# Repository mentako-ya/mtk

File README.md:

# mtk

homebrew keyboard with thumb operated trackball & rotary encoder.

mtk64el 作例
- キーキャップ:CORSAIR PBT DOUBLE-SHOT 交換用カラーキーキャップセット - 日本語108キー, Arctic White - CH-9911040-JP
- トラックボール：ぺリックス PERIPRO-303 GP 34 mm
- TRRSケーブル：https://shop.dailycraft.jp/products/trrs_cable_50_gloss
- USB Type-cケーブル：https://amzn.asia/d/h8pfZIJ

mtk64el ロープロファイル 作例

mtk64el ロープロファイル(Lofree + Chock V1) 作例
- キースイッチ(メイン部分):[LOFREE x KAILH Full POM Low Profile Switches](https://amzn.asia/d/74pwfkn)
- キーキャップ(メイン部分):[XVX ロープロファイル PBT キーキャップ](https://amzn.asia/d/7V1A6T4)
- キースイッチ(親指部分):[Kailhロープロファイルスイッチ - Pink](https://amzn.asia/d/bSlNIMm)
- キーキャップ(親指部分):[Chocfox CFX keycap](https://talpkeyboard.net/items/638b518dcc223746ee14eae8)

mtk64el Lofree Full POM ロープロファイルスイッチ取り付け例
- [LOFREE x KAILH Full POM Low Profile Switches](https://amzn.asia/d/74pwfkn)

mtk64el MX互換キースイッチ取り付け用トッププレート

mtk64el アンダーグロー

[rev3ケースプリント用3Dデータ](mtk/design/mtk64elt_STL/rev3)　/ テントスタンド[3Dデータ右](mtk/design/mtk64elt_STL/rev3/mtk64el_rev3_tent_RH.stl)　/ [3Dデータ左](mtk/design/mtk64elt_STL/rev3/mtk64el_rev3_tent_LH.stl) 

Chock V1スイッチ / Lofree Shadowスイッチ / MX互換スイッチ

[insnote](https://insnote.net)様にてmtk64eのレビューを掲載いただきました。　https://insnote.net/homebrewkeyboard-mtk64e_review/

mtk64eの使用感、カスタマイズなどご紹介いただいております。導入をご検討されている方はぜひご一読ください。

## remap対応 ファームウェア  

!!! Remap https://remap-keys.app のアップデートにより、従来のファームウェア（qmk_firmware 0.16ベース）を使用したキーボードを接続すると、エラーメッセージが表示されマッピング変更ができません。
https://remap-keys.app をご利用の場合、qmk_firmware 0.22ベースのファームウェアをご使用ください。

### qmk_firmware 0.22ベース ファームウェア https://remap-keys.app をご使用ください

#### PMW3389センサー用
<details>

- [mtk_mtk64e_PMW3389_AutoMouseLayer_via.0.22.hex](https://raw.githubusercontent.com/mentako-ya/mtk/main/mtk/mtk_mtk64e_PMW3389_AutoMouseLayer_via.0.22.hex)
 rev3基板 PMW3389センサー　左ロータリーエンコーダー、右ボール用、自動マウスレイヤー切替

- [mtk_mtk64e_PMW3389_AutoMouseLayer_via_leftball.0.22.hex](https://raw.githubusercontent.com/mentako-ya/mtk/main/mtk/mtk_mtk64e_PMW3389_AutoMouseLayer_via_leftball.0.22.hex)
 rev3基板 PMW3389センサー　右ロータリーエンコーダー、左ボール用、自動マウスレイヤー切替

- [mtk_mtk64e_PMW3389_AutoMouseLayer_via_db.0.22.hex](https://raw.githubusercontent.com/mentako-ya/mtk/main/mtk/mtk_mtk64e_PMW3389_AutoMouseLayer_via_db.0.22.hex)
 rev3基板 PMW3389センサー　左右ボール用、自動マウスレイヤー切替

- [mtk_mtk64e_PMW3389_AutoMouseLayer_via_db.0.22.hex](https://raw.githubusercontent.com/mentako-ya/mtk/main/mtk/mtk_mtk64e_PMW3389_AutoMouseLayer_via_db.0.22.hex)
 rev3基板 PMW3389センサー　左右ボール用（Master側ポインター、Slabe側スクロール）、自動マウスレイヤー切替

- [mtk_mtk64e_PMW3389_AutoMouseLayer_via_db.0.22.hex](https://raw.githubusercontent.com/mentako-ya/mtk/main/mtk/mtk_mtk64e_PMW3389_AutoMouseLayer_via_db_noscrl.0.22.hex)
 rev3基板 PMW3389センサー　左右ボール用（両側ポインター）、自動マウスレイヤー切替

</details>

#### PMW3360センサー用
<details>

- [mtk_mtk64e_PMW3360_AutoMouseLayer_via.0.22.hex](https://raw.githubusercontent.com/mentako-ya/mtk/main/mtk/mtk_mtk64e_PMW3360_AutoMouseLayer_via.0.22.hex)
 rev2基板 PMW3360センサー　左ロータリーエンコーダー、右ボール用、自動マウスレイヤー切替

- [mtk_mtk64e_PMW3360_AutoMouseLayer_via_leftball.0.22.hex](https://raw.githubusercontent.com/mentako-ya/mtk/main/mtk/mtk_mtk64e_PMW3360_AutoMouseLayer_via_leftball.0.22.hex)
 rev2基板 PMW3360センサー　右ロータリーエンコーダー、左ボール用、自動マウスレイヤー切替

- [mtk_mtk64e_PMW3360_AutoMouseLayer_via_db.0.22.hex](https://raw.githubusercontent.com/mentako-ya/mtk/main/mtk/mtk_mtk64e_PMW3360_AutoMouseLayer_via_db.0.22.hex)
 rev2基板 PMW3360センサー　左右ボール用、自動マウスレイヤー切替

- [mtk_mtk64e_PMW3360_AutoMouseLayer_via_db.0.22.hex](https://raw.githubusercontent.com/mentako-ya/mtk/main/mtk/mtk_mtk64e_PMW3360_AutoMouseLayer_via_db.0.22.hex)
 rev2基板 PMW3360センサー　左右ボール用（Master側ポインター、Slabe側スクロール）、自動マウスレイヤー切替

- [mtk_mtk64e_PMW3360_AutoMouseLayer_via_db.0.22.hex](https://raw.githubusercontent.com/mentako-ya/mtk/main/mtk/mtk_mtk64e_PMW3360_AutoMouseLayer_via_db_noscrl.0.22.hex)
 rev2基板 PMW3360センサー　左右ボール用（両側ポインター）、自動マウスレイヤー切替

</details>

!!! qmk_firmware 0.16ベースのファームウェアでRemapをご使用の場合、旧バージョンのRemap https://qmk018.remap-keys.app をご利用ください。

### qmk_firmware 0.16ベース ファームウェア https://qmk018.remap-keys.app を使用
<details>

- [mtk_mtk64_via.hex](https://raw.githubusercontent.com/mentako-ya/mtk/main/mtk/mtk_mtk64_via.hex)
 rev1基板　右ボール/左ボール/左右ボール用
   
- [mtk_mtk64e_via.hex](https://raw.githubusercontent.com/mentako-ya/mtk/main/mtk/mtk_mtk64e_via.hex)
 rev2基板 PMW3360センサー　左ロータリーエンコーダー、右ボール用

- [mtk_mtk64e_left_ball_via.hex](https://raw.githubusercontent.com/mentako-ya/mtk/main/mtk/mtk_mtk64e_left_ball_via.hex)
 rev2基板 PMW3360センサー　右ロータリーエンコーダー、左ボール用
   
- [mtk_mtk64e_AutoMouseLayer_via.hex](https://raw.githubusercontent.com/mentako-ya/mtk/main/mtk/mtk_mtk64e_AutoMouseLayer_via.hex)
 rev2基板 PMW3360センサー　左ロータリーエンコーダー、右ボール用、自動マウスレイヤー切替

- [mtk_mtk64e_AutoMouseLayer_via_db.hex](https://raw.githubusercontent.com/mentako-ya/mtk/main/mtk/mtk_mtk64e_AutoMouseLayer_via_db.hex)
 rev2基板 PMW3360センサー　左右ボール用（Master側ポインター、Slabe側スクロール）、自動マウスレイヤー切替

- [mtk_mtk64e_AutoMouseLayer_via_db_noscrl.hex](https://raw.githubusercontent.com/mentako-ya/mtk/main/mtk/mtk_mtk64e_AutoMouseLayer_via_db_noscrl.hex)
 rev2基板 PMW3360センサー　左右ボール用（両側ポインター）、自動マウスレイヤー切替
   
- [mtk_mtk64e_AutoMouseLayer_via_leftball.hex](https://raw.githubusercontent.com/mentako-ya/mtk/main/mtk/mtk_mtk64e_AutoMouseLayer_via_leftball.hex)
 rev2基板　右ロータリーエンコーダー、左ボール用、自動マウスレイヤー切替

- [mtk_mtk64e_PMW3389_AutoMouseLayer_via.hex](https://raw.githubusercontent.com/mentako-ya/mtk/main/mtk/mtk_mtk64e_PMW3389_AutoMouseLayer_via.hex)
 rev3基板 PMW3389センサー　左ロータリーエンコーダー、右ボール用、自動マウスレイヤー切替

</details>

## remap用 via.json

- [mtk64_rb_via.json](https://raw.githubusercontent.com/mentako-ya/mtk/main/mtk/mtk64_rb_via.json)     rev1 mtk64　右ボール用 
    
- [mtk64_db_via.json](https://raw.githubusercontent.com/mentako-ya/mtk/main/mtk/mtk64_db_via.json)  rev1 mtk64　左右ボール用 
    
- [mtk64e_via.json](https://raw.githubusercontent.com/mentako-ya/mtk/main/mtk/mtk64e_via.json)      rev2,rev3 mtk64e　ロータリーエンコーダー＆ボール、左右ボール用

## ご自身でファームウェアをカスタマイズ、ビルドする場合 

   [via firmware ビルドガイド](qmk_firmware/keyboards/mtk/)

## 更新情報

<details>

### mtk64el rev3ケースデータを追加しました

   [rev3ケースデータ](mtk/design/mtk64elt_STL/rev3)

### mtk64el になりました
   親指末端のキーを手前斜め下、親指側面で押下する位置に配置しました。

   親指部分にCherryMX互換キーを使用する場合でも、末端のキーのみロープロファイルで使用する設計です。
   
   全キーロープロファイル化が可能になりました。
  
   ロープロファイルキーはGateron Low Profile 2.0 (KS-33) を使用します。（Kailh chock v1は使用できません）

   トラックボールケースの形状を変更してボールが落ちにくくなりました。
   
   LEDはアンダーグローのみになりました。

   ファームウェアはmtk64eと共通です。

### ファームウェアが　qmk_firmware 0.22 ベースになりました
   ファームウェアを　qmk_firmware 0.22 ベースに更新しました。
   
   Remap [https://remap-keys.app] のアップデートに対応しました。

### トラックボールセンサーをPMW3389に更新しました
   トラックボールセンサーをより高性能なPMW3389DM-T3QUに更新しました。
   
   [PMW3360DM-T2QUとPMW3389DM-T3QUの比較](https://www.pixart.com/products-comparison/7/Optical_Mouse_Sensor)
   
   ファームウェアはPMW3389センサー用になります。
   
   従来のPMW3360センサーを使用したキーボードをご使用の場合、ファームウェアはPMW3360センサー用をご使用ください。
   
### 右ロータリーエンコーダー、左ボール用、自動マウスレイヤー切替有効　ファームウェアを追加しました

   [mtk_mtk64e_AutoMouseLayer_via_leftball.hex](https://raw.githubusercontent.com/mentako-ya/mtk/main/mtk/mtk_mtk64e_AutoMouseLayer_via_leftball.hex) rev2基板用　右ロータリーエンコーダー、左ボール用、自動マウスレイヤー切替

   ソースコード : https://github.com/mentako-ya/mtk/tree/mtk64e_leftball

### ファームウェアを再ビルドしました
   [mtk_mtk64e_AutoMouseLayer_via.hex](https://raw.githubusercontent.com/mentako-ya/mtk/main/mtk/mtk_mtk64e_AutoMouseLayer_via.hex) rev2基板用　左ロータリーエンコーダー、右ボール用、自動マウスレイヤー切替

   [mtk_mtk64e_AutoMouseLayer_via_db.hex](https://raw.githubusercontent.com/mentako-ya/mtk/main/mtk/mtk_mtk64e_AutoMouseLayer_via_db.hex) rev2基板用　左右ボール用（Master側ポインター、Slabe側スクロール）、自動マウスレイヤー切替

   [mtk_mtk64e_AutoMouseLayer_via_db_noscrl.hex](https://raw.githubusercontent.com/mentako-ya/mtk/main/mtk/mtk_mtk64e_AutoMouseLayer_via_db_noscrl.hex) rev2基板用　左右ボール用（両側ポインター）、自動マウスレイヤー切替
   
   qmk_firmwareのバージョン不整合により、キーボード接続時に初期化処理が正しく動作しない場合があったため、qmk_firmware 0.16.3 で再ビルドしました。
   再ビルドによりレイヤー３のカスタムキーコードが変わりました。ファームウェア更新した場合、キーマップをリセットするか、新しいキーコードとの対応を確認してキーマッピングを修正してください。
　
### オーディオ制御とシステム制御キーを有効化しました
   [mtk_mtk64e_AutoMouseLayer_via.hex](https://raw.githubusercontent.com/mentako-ya/mtk/main/mtk/mtk_mtk64e_AutoMouseLayer_via.hex)
   
   ご自身でファームウェアをビルドする場合、[rules.mk](https://github.com/mentako-ya/mtk/blob/cd9f4ba413dade68378f4804782a1528e7ef739e/qmk_firmware/keyboards/mtk/mtk64e/rules.mk#L12)の
   ```EXTRAKEY_ENABLE = no        # Audio control and System control```
   をyesに修正してください。
   
   ファームウェアのサイズが上限に近いため、有効化している機能の組み合わせによっては、ファイル容量オーバーによりビルドできない場合があります。

### 左右ボール用ファームウェアを追加しました。
   [mtk_mtk64e_AutoMouseLayer_via_db.hex](https://raw.githubusercontent.com/mentako-ya/mtk/main/mtk/mtk_mtk64e_AutoMouseLayer_via_db.hex) rev2基板用　左右ボール用（Master側ポインター、Slabe側スクロール）、自動マウスレイヤー切替
   [mtk_mtk64e_AutoMouseLayer_via_db_noscrl.hex](https://raw.githubusercontent.com/mentako-ya/mtk/main/mtk/mtk_mtk64e_AutoMouseLayer_via_db_noscrl.hex) rev2基板用　左右ボール用（両側ポインター）、自動マウスレイヤー切替

### 意図せずマウスレイヤー２が解除されてしまうバグに対応しました。
自動でマウスレイヤーに切り替わっている間に手動でレイヤー２に切り替えると、一定時間経過後にレイヤー２が解除されるバグに対応しました。

### エンコーダーの解像度を調整しました。
[エンコーダーの仕様](https://tech.alpsalpine.com/j/products/detail/EC11E18244AU/#ancFig3)に合わせて、'ENCODER_RESOLUTION 4 → 2' に調整しました。

### 自動マウスレイヤーから元のレイヤーに戻る時間を0.1秒単位で調整可能にしました。
調整用カスタムキーコード
- KC_TO_RESET_INC　0x5DB2
- KC_TO_RESET_DEC　0x5DB3

### トラックボール操作時に自動でマウスレイヤー2に切り替わる対応を追加しました。
[takashicompanyさんの実装](https://zenn.dev/takashicompany/articles/69b87160cda4b9)を参考にしています。

[mtk_mtk64e_AutoMouseLayer_via.hex](https://raw.githubusercontent.com/mentako-ya/mtk/main/mtk/mtk_mtk64e_AutoMouseLayer_via.hex)

※容量の都合でこちらのファームウェアはLEDエフェクトを省略しています。（LEDのOn/Off、色と明るさ調整は可能、点滅やグラデーションは不可）
LEDエフェクトが必要な場合、従来のファームウェアをご利用ください。

### 通電直後のエンコーダー誤作動対応を追加しました。

### バックプレートが透明アクリル製になりました。
バックプレート固定用の低頭6角穴付きボルトの付け外しには[T5サイズのレンチ](https://amzn.asia/d/b8Xeegc)を使用します。

### メインの基板が黒色になりました。

### 親指のロープロファイルキーの向きを内向きに変更しました。
[MCC-profile POM Choc keycap](https://shop.yushakobo.jp/products/3694)のような、シリンドリカル（円柱状に凹んでいる形状）のキーを使用できます。

[MBK Choc Low-Profile Keycaps](https://shop.yushakobo.jp/products/mbk-choc-low-profile-keycaps)のような、スフィリカル（お椀状に凹んでいる形状）のキーでは手前側の角が親指に当たって痛くなってしまう方におすすめです。（mtk64elでは使用できません）
</details>

## キーボードの接続

まず、動作確認のために右左の各キーボードを単体でPCに接続し、キー入力が可能であること、OLEDにキーボードの情報が表示されることを確認してください。（OLEDは一定時間操作しないと消灯します）

USB Type-c ケーブルは充電器や携帯電話などの製品に付属のケーブルは使用できません。USB2.0/USB3.0の表記のあるデータ通信用のケーブルを使用してください。
PCからキーボードとして認識されない場合、USBケーブルがデータ通信用ではない、USBケーブルがケースと干渉してプロマイクロにしっかり刺さっていないなどの可能性があります。

根元の形状が太いUSBケーブルや特殊な形状のUSBケーブルは、ケースと干渉する場合があります。
作例は[こちら](https://amzn.asia/d/gQuaIi1)のUSBケーブルを使用しています。

USB2.0のケーブルを使用してType-c端子にケーブルをきちんと差し込んだたうえで、接続時にキー入力できない場合やOLEDに何も表示されない場合、ロゴが表示されていてキー情報（数値やコード）が表示されない場合は、OLEDの斜め下にあるリセットボタン（ボルトの頭）をプッシュするか、キーボードを接続し直してください。

USBケーブルに問題がなく、動作しない場合は、プロマイクロのコンスルーが抜けかけている、回路がショートしていて起動できない（LEDの取り付け方向間違いでこの状態になることが多いです）などのハードウェアの問題か、ファームウェアが消えているなどのソフトウェアの問題が考えられます。

USB接続時にプロマイクロ裏側の赤いランプが点灯しているか、USB端子の隙間から確認してください。
赤いLEDが点灯していない場合、点灯してもすぐ消えてしまう場合ば、ハードウェアの問題です。

左右単体で動作確認できたら、TRSケーブルで左右を接続し、どちらか一方のUSB端子をPCに接続してください。

左右を繋ぐと動作しない場合、TRSケーブルが奥まできちんと刺さっていないか、TRSケーブルの断線、接触不良が考えられます。
TRSケーブルは、ケーブル付け根が本体のケースの中まで入り込む設計です。ねじ込むようにしてしっかり奥まで差し込んでください。

ジャックの付け根が太いケーブルやL字のケーブルはケースに干渉するため、根元の細いケーブルを使用するか、ケース側を加工する必要があります。
作例は[こちら](https://shop.dailycraft.jp/products/trrs_cable_50_gloss)のTRRSケーブルを使用しています。

スリープからの復帰の際にキーボードが動作しなくなる場合、PC側のUSB省電力設定やUSBセレクティブサスペンドをOFFにするか、OLED斜め下のリセットボタン押下、USBケーブルの再接続で復帰してください。

## キーマップ変更

キーマップの変更はChromeブラウザを使用して、https://remap-keys.app　で変更します。

（旧バージョンのqmk_firmware 0.16ベースのファームウエアをご使用の場合、https://qmk018.remap-keys.app　で変更します。）

下記に本キーボードを使用する際に最低限必要な手順を記載します。

remapの一般的な使用方法はサリチル酸さんの記事などをご参照ください。

　https://salicylic-acid3.hatenablog.com/entry/remap-manual

1. [START REMAP FOR YOUR KEYBORD]　をクリック

2. [+ KEYBORD]をクリック

3. [mtk64] か。[mtk64e]を選択して接続.

4. Jsonファイルのアップロードを求められるので、下記からレイアウトに合わせたjsonファイルをダウンロードして使用する

- mtk64 右ボール用 [mtk64_rb_via.json](https://raw.githubusercontent.com/mentako-ya/mtk/main/mtk/mtk64_rb_via.json)
- mtk64 左右ボール用 [mtk64_db_via.json](https://raw.githubusercontent.com/mentako-ya/mtk/main/mtk/mtk64_db_via.json)
- mtk64e ロータリーエンコーダー＆ボール、両側ボール用 [mtk64e_via.json](https://raw.githubusercontent.com/mentako-ya/mtk/main/mtk/mtk64e_via.json)

5. キーマップの変更 / キーマップの書き込み（右上Flashボタン） /　変更したキーマップの保存　/　キーマップのPDFダウンロード　などが可能

右ボール　キーマップサンプル

- via keyleyout(right ball) [mtk64_rb_via.json](https://raw.githubusercontent.com/mentako-ya/mtk/main/mtk/mtk64_rb_via.json)
- sample keymap cheetsheet(right ball) [mtk64_rb_keymap_cheatsheet.pdf](mtk/mtk64_rb_keymap_cheatsheet.pdf)

左右ボール　キーマップサンプル

- via keyleyout(double ball) [mtk64_db_via.json](https://raw.githubusercontent.com/mentako-ya/mtk/main/mtk/mtk64_db_via.json)
- sample keymap cheetsheet(double ball) [mtk64_db_keymap_cheatsheet.pdf](mtk/mtk64_db_keymap_cheatsheet.pdf)

mtk64e ロータリーエンコーダー＆ボール、左右ボール　キーマップサンプル

- via keyleyout(rotary encoder) [mtk64e_via.json](https://raw.githubusercontent.com/mentako-ya/mtk/main/mtk/mtk64e_via.json)
- sample keymap cheetsheet(rotary encoder) [mtk64e_keymap_cheatsheet.pdf](mtk/mtk64e_keymap_cheatsheet.pdf)
- sample keymap cheetsheet(rotary encoder) [mtk64e_AutoMouseLayer_keymap_cheatsheet.pdf](mtk/mtk64e_AutoMouseLayer_keymap_cheatsheet.pdf)

※ 製品出荷時点でキーボードに設定済みのマッピングは、ファームウェアのデフォルトキーマッピングとは一部異なる場合があります。

キーマップのリセットや、キーボードの初期化を行うと、キーマップはファームウェアのデフォルトキーマップにリセットされます。

キーマップ変更やリセットを行う前に、初期のマッピングの状態でマップの保存をお勧めします。

## ファームウェア更新
[Pro Micro Web Updater](https://sekigon-gonnoc.github.io/promicro-web-updater/index.html) を使用してファームウェアを更新できます。

出荷時に書き込まれているファームウェアは[mtk_mtk64e_AutoMouseLayer_via.hex](https://raw.githubusercontent.com/mentako-ya/mtk/main/mtk/mtk_mtk64e_AutoMouseLayer_via.hex)になります。　

[Pro Micro Web Updater](https://sekigon-gonnoc.github.io/promicro-web-updater/index.html) にアクセスし、事前にダウンロードしたファームウェアをアップロードします。

キーボードの左右どちらか一方をUSB接続し、画面上の[flash]ボタンを押下します。

シリアルポートへの接続要求のウインドウが表示されるので、OLED斜め下のリセットスイッチ（ボルトの頭）を２回連続でクリックします。

シリアルポートの一覧に「Pro Micro 5v」が表示されるので、選択して接続ボタンを押下します。

## 基本的な使用方法

本キーボードは、レイヤー０〜3の４種類のキーマップを切り替えて使用します。

レイヤーの切り替えは左手親指キーのHOLD（シフトキーのように押したままにすること）に割り当てられており、左端からLayer(1),Layer(2),Layer(3)が設定されています。

- レイヤー０:通常のアルファベット入力
- レイヤー１:Shiftキー押下相当（大文字入力や記号入力）
- レイヤー２:右手のキーがマウスのボタンに切り替わる
- レイヤー３:トラックボールがスクロールモードに切り替わる、キースイッチはLEDの調整、トラックボールの速度、スクロールの速度調整

自動マウスレイヤー切替に対応したファームウェアでは、トラックボールを一定距離動かすと自動的にレイヤー2に切り替わり、マウスボタンクリックが可能になります。
デフォルトでは１秒間何も操作しないとレイヤー0に戻ります。
自動マウスレイヤー切替機能がOnの場合、OLED３行目が反転表示されます。
（レイヤー３左側のキーボード最下段左から２番目のキーで自動切替機能On／Off）

## レイヤー３トラックボール設定のコード値
レイヤー３にマッピングされているキーのうち、トラックボールの設定を行うキーは、のカスタムコードで設定します。
Remapでは User0 ~（旧バージョンRemapでは16進数）で設定します。

コード値については下記の表を参照してください。

- RemapのUserキー:旧バージョンRemapの16進コード:keymap.cのカスタムコード　

### レイヤー３トラックボール設定のコード値　mtk64　（mtk_mtk64_via.hex/mtk_mtk64e_via.hex）
- User 0:0x5DA5:KBC_RST    トラックボール設定リセット
- User 1:0x5DA6:KBC_SAVE   トラックボール設定保存（次回接続時にトラックボール設定が保存された値になっている）
- User 2:0x5DA7:CPI_I100   トラックボールのカーソル速度 +100
- User 3:0x5DA8:CPI_D100   トラックボールのカーソル速度 -100
- User 4:0x5DA9:CPI_I1K    トラックボールのカーソル速度  +1000
- User 5:0x5DAA:CPI_D1K    トラックボールのカーソル速度 -1000
- User 6:0x5DAB:SCRL_TO    トラックボールのスクロールモードOn/Off
- User 7:0x5DAC:SCRL_MO    トラックボールのスクロールモードOn
- User 8:0x5DAD:SCRL_DVI   トラックボールのスクロール速度を下げる
- User 9:0x5DAE:SCRL_DVD   トラックボールのスクロール速度を上げる

### レイヤー３トラックボール設定のコード値　mtk64e自動マウスレイヤー　（mtk_mtk64e_AutoMouseLayer_via.0.22.hex）
- User 0:0x5DB1:KBC_RST    トラックボール設定リセット
- User 1:0x5DB2:KBC_SAVE   トラックボール設定保存（次回接続時にトラックボール設定が保存された値になっている）
- User 2:0x5DB3:CPI_I100   トラックボールのカーソル速度 +100
- User 3:0x5DB4:CPI_D100   トラックボールのカーソル速度 -100
- User 4:0x5DB5:CPI_I1K    トラックボールのカーソル速度 +1000
- User 5:0x5DB6:CPI_D1K    トラックボールのカーソル速度 -1000
- User 6:0x5DB7:SCRL_TO    トラックボールのスクロールモードOn/Off
- User 7:0x5DB8:SCRL_MO    トラックボールのスクロールモードOn
- User 8:0x5DB9:SCRL_DVI   トラックボールのスクロール速度を下げる
- User 9:0x5DBA:SCRL_DVD   トラックボールのスクロール速度を上げる

### レイヤー３自動マウスレイヤー切替設定のコード値　mtk64e自動マウスレイヤー　（mtk_mtk64e_AutoMouseLayer_via.0.22.hex）
- User10:0x5DBB:KC_TG_CLICKABLE     自動マウスレイヤー切替On/Off (有効時にOLEDを反転表示）
- User11:0x5DBC:KC_TO_CLICKABLE_INC 自動マウスレイヤー切替距離 +
- User12:0x5DBD:KC_TO_CLICKABLE_DEC 自動マウスレイヤー切替距離 -
- User13:0x5DBE:KC_TO_RESET_INC     自動マウスレイヤーから元のレイヤーに戻る時間 + 0.1秒
- User14:0x5DBF:KC_TO_RESET_DEC.    自動マウスレイヤーから元のレイヤーに戻る時間 - 0.1秒
 
## 左右トラックボール構成の動作

[mtk_mtk64e_AutoMouseLayer_via_db.hex](https://raw.githubusercontent.com/mentako-ya/mtk/main/mtk/mtk_mtk64e_AutoMouseLayer_via_db.hex) を使用するとUSBケーブルを挿した側（Master)がポインター操作、反対側（Slave）がスクロール操作（上下左右）になります。
レイヤー３に切り替えた際に左右のモードが入れ替わります。

[mtk_mtk64e_AutoMouseLayer_via_db_noscrl.hex](https://raw.githubusercontent.com/mentako-ya/mtk/main/mtk/mtk_mtk64e_AutoMouseLayer_via_db_noscrl.hex) を使用するとMaster側Slave側ともポインター操作になります。
レイヤー３に切り替えた際に左右ともスクロールになります。

## トラックボールのお手入れ
ボールとボールケースの白い支持球はこまめに掃除していただくと、滑りがよくなり快適に使用できます。

白い支持球周辺に埃が溜まりますので、時々ボールを外してメガネ拭きなどで掃除してください。
ボールの滑りが悪いと、狙ったところをカーソルが飛び越してしまい、使いづらくなります。

ボールに[シリコンスプレー](https://amzn.asia/d/2fwdtvX)を少量塗布して、ティッシュ、メガネ拭き、[キムワイプ](https://www.amazon.co.jp/dp/B001EHI9XI)などで軽く拭っていただくと、滑りが良くなり、操作性が向上します。

定期的にシリコンを塗布する必要がありますが、シリコンスプレーは1本あれば数年使用できます。

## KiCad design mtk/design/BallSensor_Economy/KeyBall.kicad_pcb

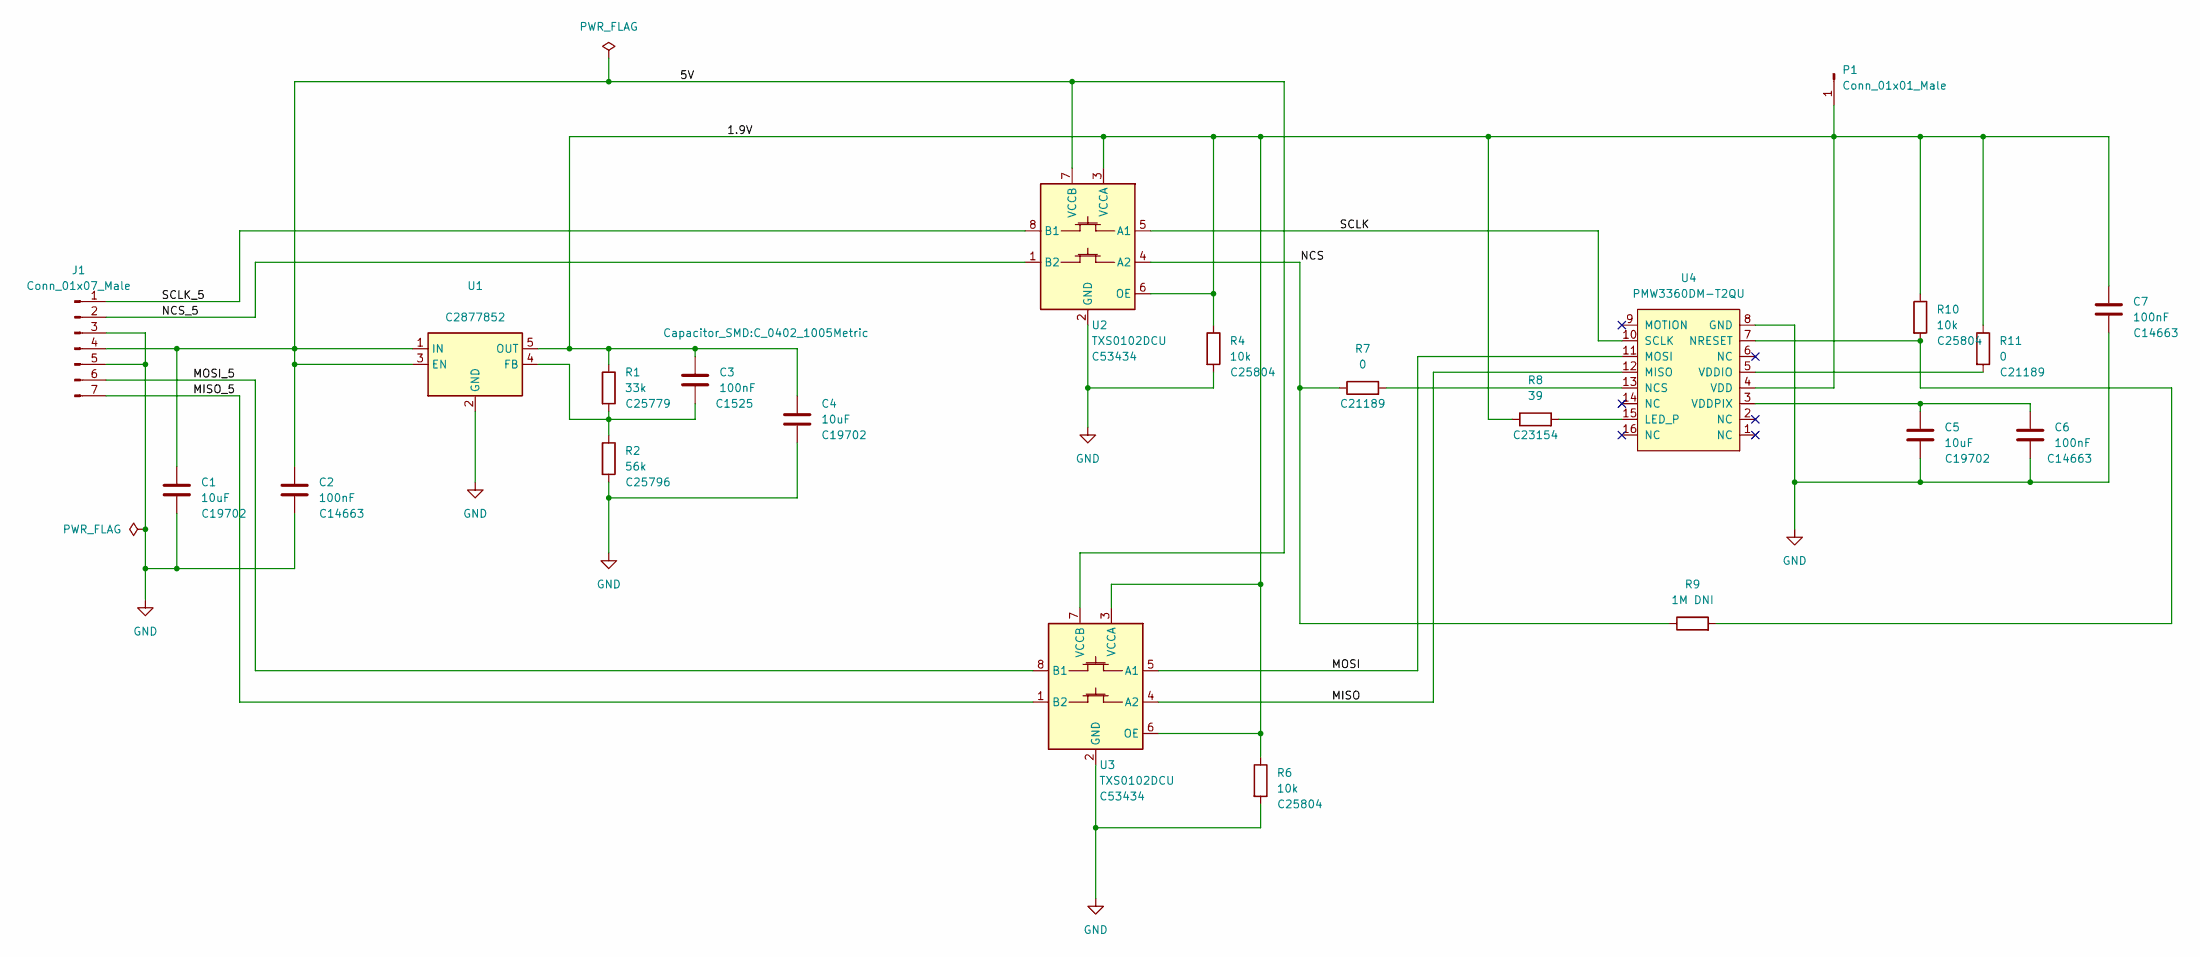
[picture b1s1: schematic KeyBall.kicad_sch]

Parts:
C1, C4, C5: 10uF; C_0603_1608Metric; LCSC C19702
C2, C6, C7: 100nF; C_0603_1608Metric; LCSC C14663
C3: 100nF; C_0402_1005Metric; LCSC C1525
J1: Conn_01x07_Male; PinHeader_1x07_P2.54mm_Vertical
P1: Conn_01x01_Male; TestPoint_Pad_D1.0mm
R1: 33k; R_0402_1005Metric; LCSC C25779
R2: 56k; R_0402_1005Metric; LCSC C25796
R4, R6, R10: 10k; R_0603_1608Metric; LCSC C25804
R7, R11: 0; R_0603_1608Metric; LCSC C21189
R8: 39; R_0603_1608Metric; LCSC C23154
R9: 1M DNI; R_0603_1608Metric
U1: LCSC C2877852
U2, U3: TXS0102DCU; VSSOP-8_2.3x2mm_P0.5mm; LCSC C53434
U4: PMW3360DM-T2QU; IC_PMW3360DM-T2QU_noEdge

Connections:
/1.9V: C3.1, C4.1, C7.1, P1.1, R1.1, R4.1, R6.1, R8.1, R10.1, R11.1, U1.5 (OUT), U2.3 (VCCA), U2.6 (OE), U3.3 (VCCA), U3.6 (OE), U4.4 (VDD)
/5V: C1.1, C2.1, J1.4, U1.1 (IN), U1.3 (EN), U2.7 (VCCB), U3.7 (VCCB)
/MISO: U3.4 (A2), U4.12 (MISO)
/MISO_5: J1.7, U3.1 (B2)
/MOSI: U3.5 (A1), U4.11 (MOSI)
/MOSI_5: J1.6, U3.8 (B1)
/NCS: R7.1, R9.1, U2.4 (A2)
/NCS_5: J1.2, U2.1 (B2)
/SCLK: U2.5 (A1), U4.10 (SCLK)
/SCLK_5: J1.1, U2.8 (B1)
GND: C1.2, C2.2, C4.2, C5.2, C6.2, C7.2, J1.3, J1.5, R2.2, R4.2, R6.2, U1.2 (GND), U2.2 (GND), U3.2 (GND), U4.8 (GND)
unnamed: C3.2, R1.2, R2.1, U1.4 (FB)
unnamed: C5.1, C6.1, U4.3 (VDDPIX)
unnamed: R7.2, U4.13 (NCS)
unnamed: R8.2, U4.15 (LED_P)
unnamed: R9.2, R10.2, U4.7 (NRESET)
unnamed: R11.2, U4.5 (VDDIO)

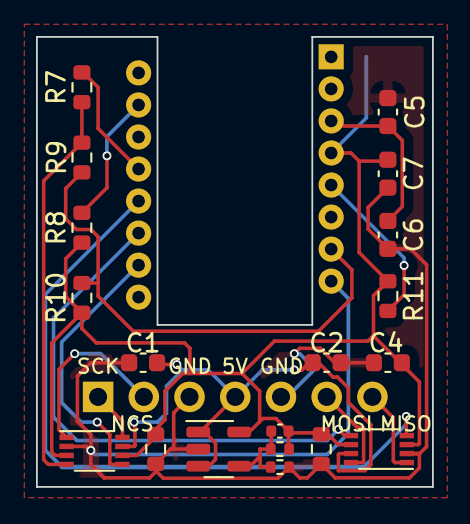
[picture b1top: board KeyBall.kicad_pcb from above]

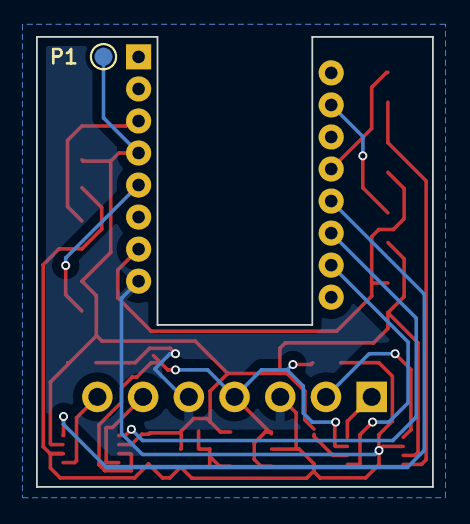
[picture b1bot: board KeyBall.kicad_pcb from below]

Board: 2 copper layers, 22.0 x 25.0 mm, 22 parts (2 on the bottom side), 17 nets.

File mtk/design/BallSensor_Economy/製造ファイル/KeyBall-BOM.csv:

Comment,Designator,Footprint,LCSC
"10uF","C1,C4,C5","Capacitor_SMD:C_0603_1608Metric","C19702"
"100nF","C2,C6,C7","Capacitor_SMD:C_0603_1608Metric","C14663"
"100nF","C3","Capacitor_SMD:C_0402_1005Metric","C1525"
"33k","R1","Resistor_SMD:R_0402_1005Metric","C25779"
"56k","R2","Resistor_SMD:R_0402_1005Metric","C25796"
"10k","R4,R6,R10","Resistor_SMD:R_0603_1608Metric"," C25804"
"0","R7,R11","Resistor_SMD:R_0603_1608Metric","C21189"
"39","R8","Resistor_SMD:R_0603_1608Metric","C23154"
"TPS73601DBV","U1","Package_TO_SOT_SMD:SOT-23-5","C59200"
"TXS0102DCU","U2,U3","Package_SO:VSSOP-8_2.3x2mm_P0.5mm","C53434"

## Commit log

2022-09-10 左右両ボール用via.json
2022-09-10 mtk64 double ball keymap cheetsheet追加
2022-09-10 add keymap image
2022-09-12 add right ball keymap
2022-09-12 add remap img
2022-09-24 define TAP_CODE_DELAY for common keymaps #132 https://github.com/Yowkees/keyball/pull/132 matrix_mask修正 Row4 Col3 使用可能
2022-09-25 Encoder有効 Console有効 RGB無効
2022-10-02 ピンアサイン修正
2022-10-02 TRACKBALL_DRIVER_DISABLE
2022-10-02 readme修正
2022-10-02 コンソール出力無効化
2022-10-08 KiCadデータ追加
2022-10-08 B5 配線追加
2022-10-08 親指追加キーのダイオード反転
2022-10-10 シルクプリント追加、ペースト追加 JCLPCB order
2022-10-10 コミット漏れ追加
2022-10-15 Edge.Cut修正
2022-10-18 mtk64_rev2 STL 初期コミット
2022-10-18 エッジ修正
2022-10-22 左右ロータリーエンコーダーレイアウトマッピング
2022-10-23 キーマップ修正
2022-10-23 Encoder周辺修正
2022-10-24 エンコーダーマッピング修正
2022-10-24 レイアウトをDual固定に変更
2022-10-24 mtk64eに名称変更
2022-10-24 mtk64eキーマップチートシート
2022-10-24 キーマッピング修正
2022-10-26 配線漏れ修正 geverファイル再出力
2022-10-26 readme mtk64e追加
2022-10-26 readme イメージファイル修正
2022-11-06 mtk64e左ボールファームウェア
2022-11-06 mtk64e左ボールファームウェア追加
2022-11-07 親指ロープロケース
2022-11-11 Update README.md
    トラックボール設定のコード値 mtk64e 追記
2022-11-12 Update README.md
    キーボードの接続について追記
2022-11-19 mtk64e lowprofile case data
2022-11-19 左ボール時 B2 MOSI 配線修正
2022-11-19 親指キーフットプリント置き換え準備
2022-11-22 親指キー内向きに変更
2022-11-26 ケースデータ修正 親指キーの向き修正
2022-11-26 バックプレートアクリルカットデータ追加
2022-11-26 gbrファイル更新11/20発注分
2022-11-26 KeyCadバックアップファイル削除
2022-11-30 elecrow order
2022-11-30 design folder remove
2023-01-01 fix product infomation
2023-01-02 Update /lib/keyball. Fix compile error in MOUSEKEY_ENABLE.
2023-01-03 fix leyout
2023-01-21 ボール操作でレイヤー２に切り替え https://zenn.dev/takashicompany/articles/69b87160cda4b9ru
    エンコーダー誤作動対応
2023-01-21 キーマップ修正、コード整理
2023-01-21 define AUTO_MOUSE_LEYER_ENABLE
2023-01-21 エンコーダー誤作動対応
2023-01-21 README 自動マウスレイヤー切替機能について追記
2023-01-21 自動マウスレイヤー切替操作方法追記
2023-01-23 ファームウェア更新手順追記
2023-01-29 uf2テストビルド
2023-02-04 STLファイル
2023-02-04 DXFファイル
2023-02-04 web_updaterイメージ
2023-02-13 Update README.md
    レイヤー３トラックボール設定のコード値mtk64e 修正
2023-02-14 ビルドエラー解消 typo修正
2023-02-14 自動マウスレイヤーから元のレイヤーに戻る時間を調整可能とした
2023-02-14 ファームウエアビルド、チートシート更新
2023-02-17 エンコーダーの解像度を調整
2023-02-24 意図せずマウスレイヤーが解除されてしまうバグに対応
2023-04-13 イメージ写真追加
2023-04-13 エンコーダー写真追加
2023-04-13 Update README.md
    <img width="１０００" src="mtk/photo/mtk64e.JPG">
    <img width="500" src="mtk/photo/encoder.JPG"> <img width="500" src="mtk/photo/bord.JPG">
    <img width="500" src="mtk/photo/type-c.JPG">
2023-04-14 EC11N1524402エンコーダー用ノブ追加
2023-04-21 mtk64e回路図
2023-04-22 両側ボール スレーブ側スクロール無効化ファームウェア
2023-04-22 両側ボール片側スクロールファームウェア
2023-04-22 readme更新
2023-04-23 EXTRAKEY_ENABLE = yes に変更
2023-04-24 Update README.md
    https://usevia.app/ にvia.jsonが未対応、remapのみ対応
2023-04-29 qmk_firmware 0.16.3 で再ビルド
2023-04-29 チートシート更新
2023-05-07 PMW3360 PMW3389データシート追加
2023-05-07 PMW3360をPMW3389に単純置き換え
2023-05-09 CPI設定をPMW3389用に変更
2023-05-09 PMW3389用ファームウェア
2023-05-09 PMW3389用ファームウェア
    (cherry picked from commit a47fa8e03afe2ff82184409e51c3747fd2e19349)
2023-05-09 Update README.md
    (cherry picked from commit dcb24d98dfbbae9206f5b11e6501eba01f7c78a5)
2023-07-02 via用Jsonファイル追加
2023-07-05 右ロータリーエンコーダー、左ボール用、自動マウスレイヤー切替有効 ファームウェア追加
2023-07-05 右ロータリーエンコーダー、左ボール用、自動マウスレイヤー切替有効 ファームウェア再ビルド
2023-07-06 初期化処理修正
2023-07-06 自動マウスレイヤー切り替えファームウェア キーコード更新
2023-09-15 Update README.md
    https://qmk018.remap-keys.app
2023-09-16 qmk_firmware 0.22 Update
2023-09-18 左右エンコーダー、トラックボール設定整理
    via_db削除
    エンコーダー誤作動防止修正
    hexファイル追加
2023-09-18 revert d307095
    revert PMW3389 modified
2023-09-18 Revert "PMW3360をPMW3389に単純置き換え"
    This reverts commit d307095ab6337204577a4dc68d20154a539fa955.
2023-09-18 PMW3360用hexファイル追加
2023-10-11 encoder_update_user 不具合修正
2023-10-11 mtk_mtk64e_PMW33xx_AutoMouseLayer_via.0.22.hex 再ビルド
2023-11-15 mtk64el readme 3Dデータ追加
2023-11-15 更新履歴追記
2023-11-15 no message
2023-11-26 mtk64el ケースデータ更新
2023-11-26 Gateron_Upgrade_Low_Profile_switch_Hot-swap_PCB_2.0_Socket FootPrint
2023-11-26 Gateron_Upgrade_Low_Profile_switch_Hot-swap_PCB_2.0_Socket DataSheet
2024-01-04 mtk64elt_STL/rev2 ファイル更新
2024-02-05 mtk64erp 初期コミット Duprex key matrix Encoder enable
2024-02-10 readme更新 mtk64el rev3 ケースデータ
2024-02-10 画像サイズ修正
2024-03-03 プリント設定変更
2024-03-09 PMW3389対応
2024-03-12 マトリックス修正
2024-03-12 RP2040ProMicro データシート
2024-03-14 レイアウト修正
2024-03-20 ケースデータ更新
2024-04-28 ENCODER_MAP_ENABLE 対応中
2024-04-28 encoder_map_test
2024-04-30 via.json追加
2024-05-01 左右判定 GP23toGP21
2024-05-01 右エンコーダーマッピング、レイアウト微調整
2024-05-01 OLED実装 トラックボール操作方向修正
2024-05-02 トラックボール設定修正
2024-05-02 POINTING_DEVICE_LEFT
2024-05-04 左右トラックボール OLEDキー情報出力
2024-05-06 RGBLIGHT_ENABLE
2024-05-11 エンコーダーPushキーマップ変更
2024-06-22 左右判定修正
